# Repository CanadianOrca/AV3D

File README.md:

# AV3D
AV3D or Avid as is our nickname, is an acoustophoretic volumetric display. It will be able to display 3D objects using acoustic radiation forces to levitate and rapidly move a small physical particle. We utilize a fast computer and synchronized LEDs to iterate a Persistence of Vision effect, making the fast bead appear 3D.

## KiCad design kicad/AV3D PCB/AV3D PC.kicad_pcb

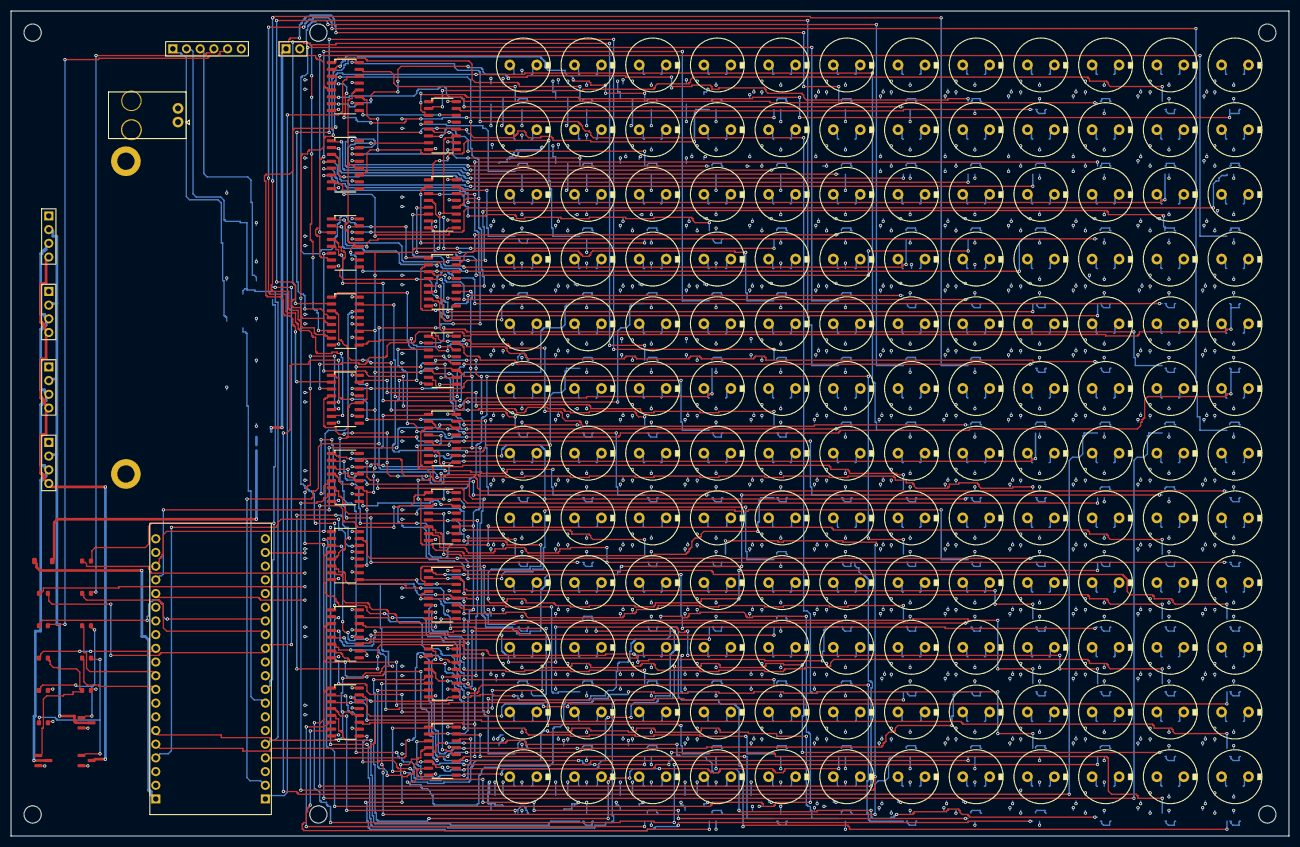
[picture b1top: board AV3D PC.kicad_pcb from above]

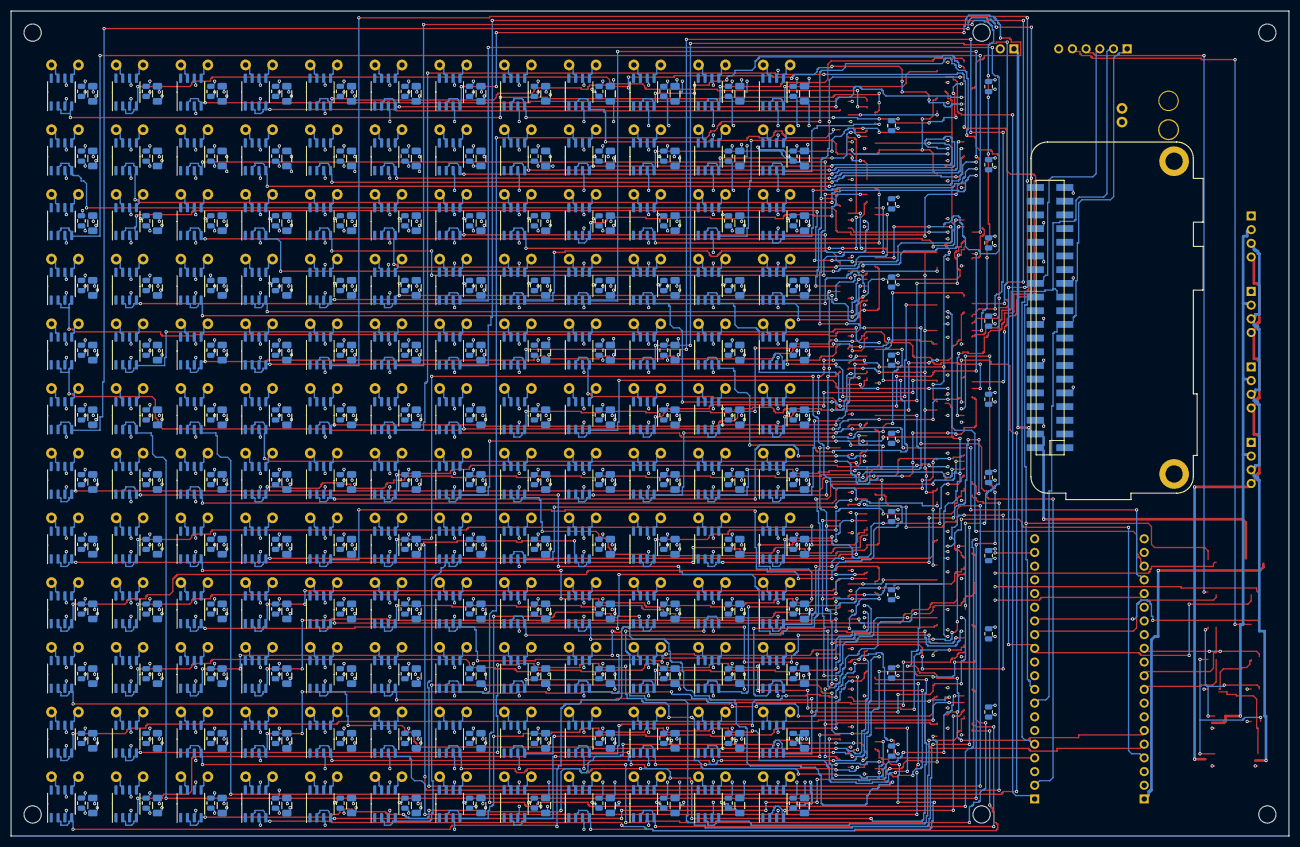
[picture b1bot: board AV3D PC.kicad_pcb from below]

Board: 4 copper layers, 237.0 x 153.0 mm, 641 parts (451 on the bottom side), 474 nets.

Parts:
A1: Raspberry_Pi_2_3; Raspberry_Pi_Zero_Socketed_THT_MountingHoles_SMT
A2: Tang Nano 20K; TangNano20K_2x20
C1, C2, C3, C4, C5, C6, C7, C8, C9, C10, C11, C12, C13, C14, C15, C16, C17, C18, C19, C20, C21, C22, C23, C24, C25, C26, C27, C28, C29, C30, C31, C32, C33, C34, C35, C36, C37, C38, C39, C40, C41, C42, C43, C44, C45, C46, C47, C48, C49, C50, C51, C52, C53, C54, C55, C56, C57, C58, C59, C60, C61, C62, C63, C64, C65, C66, C67, C68, C69, C70, C71, C72, C73, C74, C75, C76, C77, C78, C79, C80, C81, C82, C83, C84, C85, C86, C87, C88, C89, C90, C91, C92, C93, C94, C95, C96, C97, C98, C99, C100, C101, C102, C103, C104, C105, C106, C107, C108, C109, C110, C111, C112, C113, C114, C115, C116, C117, C118, C119, C120, C121, C122, C123, C124, C125, C126, C127, C128, C129, C130, C131, C132, C133, C134, C135, C136, C137, C138, C139, C140, C141, C142, C143, C144: 4.7uF, 35V; C_1206_3216Metric
C145, C146, C147, C148, C149, C150, C151, C152, C153, C154, C155, C156, C157, C158, C159, C160, C161, C162, C163, C164, C165, C166, C167, C168, C169, C170, C171, C172, C173, C174, C175, C176, C177, C178, C179, C180, C181, C182, C183, C184, C185, C186, C187, C188, C189, C190, C191, C192, C193, C194, C195, C196, C197, C198, C199, C200, C201, C202, C203, C204, C205, C206, C207, C208, C209, C210, C211, C212, C213, C214, C215, C216, C217, C218, C219, C220, C221, C222, C223, C224, C225, C226, C227, C228, C229, C230, C231, C232, C233, C234, C235, C236, C237, C238, C239, C240, C241, C242, C243, C244, C245, C246, C247, C248, C249, C250, C251, C252, C253, C254, C255, C256, C257, C258, C259, C260, C261, C262, C263, C264, C265, C266, C267, C268, C269, C270, C271, C272, C273, C274, C275, C276, C277, C278, C279, C280, C281, C282, C283, C284, C285, C286, C287, C288, C289, C290, C291, C292, C293, C294, C295, C296, C297, C298, C299, C300, C301, C302, C303, C304, C305, C306: 0.1uF, 35V; C_0805_2012Metric
D1: 1N5819WS; D_SOD-123
H1, H2, H3, H4, H5, H6: MountingHole; MountingHole_3.2mm_M3
J1: Power; Molex_70555_RA_1x02_P2.54
J2: LED 1 (12V common anode); PinHeader_1x04_P2.54mm_Vertical
J3: LED 2 (12V common anode); PinHeader_1x04_P2.54mm_Vertical
J4: LED 3 (12V common anode); PinHeader_1x04_P2.54mm_Vertical
J5: LED 4 (12V common anode); PinHeader_1x04_P2.54mm_Vertical
J6: BOARD LINK; PinHeader_1x06_P2.54mm_Vertical
J7: 5V IN; PinHeader_1x02_P2.54mm_Vertical
LS1, LS2, LS3, LS4, LS5, LS6, LS7, LS8, LS9, LS10, LS11, LS12, LS13, LS14, LS15, LS16, LS17, LS18, LS19, LS20, LS21, LS22, LS23, LS24, LS25, LS26, LS27, LS28, LS29, LS30, LS31, LS32, LS33, LS34, LS35, LS36, LS37, LS38, LS39, LS40, LS41, LS42, LS43, LS44, LS45, LS46, LS47, LS48, LS49, LS50, LS51, LS52, LS53, LS54, LS55, LS56, LS57, LS58, LS59, LS60, LS61, LS62, LS63, LS64, LS65, LS66, LS67, LS68, LS69, LS70, LS71, LS72, LS73, LS74, LS75, LS76, LS77, LS78, LS79, LS80, LS81, LS82, LS83, LS84, LS85, LS86, LS87, LS88, LS89, LS90, LS91, LS92, LS93, LS94, LS95, LS96, LS97, LS98, LS99, LS100, LS101, LS102, LS103, LS104, LS105, LS106, LS107, LS108, LS109, LS110, LS111, LS112, LS113, LS114, LS115, LS116, LS117, LS118, LS119, LS120, LS121, LS122, LS123, LS124, LS125, LS126, LS127, LS128, LS129, LS130, LS131, LS132, LS133, LS134, LS135, LS136, LS137, LS138, LS139, LS140, LS141, LS142, LS143, LS144: Speaker_Ultrasound; MSO-P1040H07T
Q1, Q2, Q3: AO3400A; SOT-23
R1, R2: 10k; R_0603_1608Metric
R3, R4, R5, R6, R7: 100; R_0603_1608Metric
R8, R9, R10: 100k; R_0603_1608Metric
U1, U2, U3, U4, U5, U6, U7, U8, U9, U10, U11, U12, U13, U14, U15, U16, U17, U18, U19, U20, U21, U22, U23, U24, U25, U26, U27, U28, U29, U30, U31, U32, U33, U34, U35, U36, U37, U38, U39, U40, U41, U42, U43, U44, U45, U46, U47, U48, U49, U50, U51, U52, U53, U54, U55, U56, U57, U58, U59, U60, U61, U62, U63, U64, U65, U66, U67, U68, U69, U70, U71, U72, U73, U74, U75, U76, U77, U78, U79, U80, U81, U82, U83, U84, U85, U86, U87, U88, U89, U90, U91, U92, U93, U94, U95, U96, U97, U98, U99, U100, U101, U102, U103, U104, U105, U106, U107, U108, U109, U110, U111, U112, U113, U114, U115, U116, U117, U118, U119, U120, U121, U122, U123, U124, U125, U126, U127, U128, U129, U130, U131, U132, U133, U134, U135, U136, U137, U138, U139, U140, U141, U142, U143, U144: TC4428A; SO-8_3.9x4.9mm_P1.27mm
U145, U146, U147, U148, U149, U150, U151, U152, U153, U154, U155, U156, U157, U158, U159, U160, U161, U162: 74AHC595; SOIC-16_3.9x9.9mm_P1.27mm

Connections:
+3V3: A2.16, A2.39, C289.1, C290.1, C291.1, C292.1, C293.1, C294.1, C295.1, C296.1, C297.1, C298.1, C299.1, C300.1, C301.1, C302.1, C303.1, C304.1, C305.1, C306.1, R1.1, R2.1, U145.10, U145.16, U146.10, U146.16, U147.10, U147.16, U148.10, U148.16, U149.10, U149.16, U150.10, U150.16, U151.10, U151.16, U152.10, U152.16, U153.10, U153.16, U154.10, U154.16, U155.10, U155.16, U156.10, U156.16, U157.10, U157.16, U158.10, U158.16, U159.10, U159.16, U160.10, U160.16, U161.10, U161.16, U162.10, U162.16
+5V: A1.2, A1.4, D1.2, J7.1
+5V_TANG: A2.1, D1.1
+12V: C1.1, C2.1, C3.1, C4.1, C5.1, C6.1, C7.1, C8.1, C9.1, C10.1, C11.1, C12.1, C13.1, C14.1, C15.1, C16.1, C17.1, C18.1, C19.1, C20.1, C21.1, C22.1, C23.1, C24.1, C25.1, C26.1, C27.1, C28.1, C29.1, C30.1, C31.1, C32.1, C33.1, C34.1, C35.1, C36.1, C37.1, C38.1, C39.1, C40.1, C41.1, C42.1, C43.1, C44.1, C45.1, C46.1, C47.1, C48.1, C49.1, C50.1, C51.1, C52.1, C53.1, C54.1, C55.1, C56.1, C57.1, C58.1, C59.1, C60.1, C61.1, C62.1, C63.1, C64.1, C65.1, C66.1, C67.1, C68.1, C69.1, C70.1, C71.1, C72.1, C73.1, C74.1, C75.1, C76.1, C77.1, C78.1, C79.1, C80.1, C81.1, C82.1, C83.1, C84.1, C85.1, C86.1, C87.1, C88.1, C89.1, C90.1, C91.1, C92.1, C93.1, C94.1, C95.1, C96.1, C97.1, C98.1, C99.1, C100.1, C101.1, C102.1, C103.1, C104.1, C105.1, C106.1, C107.1, C108.1, C109.1, C110.1, C111.1, C112.1, C113.1, C114.1, C115.1, C116.1, C117.1, C118.1, C119.1, C120.1, C121.1, C122.1, C123.1, C124.1, C125.1, C126.1, C127.1, C128.1, C129.1, C130.1, C131.1, C132.1, C133.1, C134.1, C135.1, C136.1, C137.1, C138.1, C139.1, C140.1, C141.1, C142.1, C143.1, C144.1, C145.1, C146.1, C147.1, C148.1, C149.1, C150.1, C151.1, C152.1, C153.1, C154.1, C155.1, C156.1, C157.1, C158.1, C159.1, C160.1, C161.1, C162.1, C163.1, C164.1, C165.1, C166.1, C167.1, C168.1, C169.1, C170.1, C171.1, C172.1, C173.1, C174.1, C175.1, C176.1, C177.1, C178.1, C179.1, C180.1, C181.1, C182.1, C183.1, C184.1, C185.1, C186.1, C187.1, C188.1, C189.1, C190.1, C191.1, C192.1, C193.1, C194.1, C195.1, C196.1, C197.1, C198.1, C199.1, C200.1, C201.1, C202.1, C203.1, C204.1, C205.1, C206.1, C207.1, C208.1, C209.1, C210.1, C211.1, C212.1, C213.1, C214.1, C215.1, C216.1, C217.1, C218.1, C219.1, C220.1, C221.1, C222.1, C223.1, C224.1, C225.1, C226.1, C227.1, C228.1, C229.1, C230.1, C231.1, C232.1, C233.1, C234.1, C235.1, C236.1, C237.1, C238.1, C239.1, C240.1, C241.1, C242.1, C243.1, C244.1, C245.1, C246.1, C247.1, C248.1, C249.1, C250.1, C251.1, C252.1, C253.1, C254.1, C255.1, C256.1, C257.1, C258.1, C259.1, C260.1, C261.1, C262.1, C263.1, C264.1, C265.1, C266.1, C267.1, C268.1, C269.1, C270.1, C271.1, C272.1, C273.1, C274.1, C275.1, C276.1, C277.1, C278.1, C279.1, C280.1, C281.1, C282.1, C283.1, C284.1, C285.1, C286.1, C287.1, C288.1, J1.1, J2.1, J3.1, J4.1, J5.1, U1.6, U2.6, U3.6, U4.6, U5.6, U6.6, U7.6, U8.6, U9.6, U10.6, U11.6, U12.6, U13.6, U14.6, U15.6, U16.6, U17.6, U18.6, U19.6, U20.6, U21.6, U22.6, U23.6, U24.6, U25.6, U26.6, U27.6, U28.6, U29.6, U30.6, U31.6, U32.6, U33.6, U34.6, U35.6, U36.6, U37.6, U38.6, U39.6, U40.6, U41.6, U42.6, U43.6, U44.6, U45.6, U46.6, U47.6, U48.6, U49.6, U50.6, U51.6, U52.6, U53.6, U54.6, U55.6, U56.6, U57.6, U58.6, U59.6, U60.6, U61.6, U62.6, U63.6, U64.6, U65.6, U66.6, U67.6, U68.6, U69.6, U70.6, U71.6, U72.6, U73.6, U74.6, U75.6, U76.6, U77.6, U78.6, U79.6, U80.6, U81.6, U82.6, U83.6, U84.6, U85.6, U86.6, U87.6, U88.6, U89.6, U90.6, U91.6, U92.6, U93.6, U94.6, U95.6, U96.6, U97.6, U98.6, U99.6, U100.6, U101.6, U102.6, U103.6, U104.6, U105.6, U106.6, U107.6, U108.6, U109.6, U110.6, U111.6, U112.6, U113.6, U114.6, U115.6, U116.6, U117.6, U118.6, U119.6, U120.6, U121.6, U122.6, U123.6, U124.6, U125.6, U126.6, U127.6, U128.6, U129.6, U130.6, U131.6, U132.6, U133.6, U134.6, U135.6, U136.6, U137.6, U138.6, U139.6, U140.6, U141.6, U142.6, U143.6, U144.6
CH1: U1.2, U1.4, U145.15
CH2: U2.2, U2.4, U145.1
CH3: U3.2, U3.4, U145.2
CH4: U4.2, U4.4, U145.3
CH5: U5.2, U5.4, U145.4
CH6: U6.2, U6.4, U145.5
CH7: U7.2, U7.4, U145.6
CH8: U8.2, U8.4, U145.7
CH9: U9.2, U9.4, U146.15
CH10: U10.2, U10.4, U146.1
CH11: U11.2, U11.4, U146.2
CH12: U12.2, U12.4, U146.3
CH13: U13.2, U13.4, U146.4
CH14: U14.2, U14.4, U146.5
CH15: U15.2, U15.4, U146.6
CH16: U16.2, U16.4, U146.7
CH17: U17.2, U17.4, U147.15
CH18: U18.2, U18.4, U147.1
CH19: U19.2, U19.4, U147.2
CH20: U20.2, U20.4, U147.3
CH21: U21.2, U21.4, U147.4
CH22: U22.2, U22.4, U147.5
CH23: U23.2, U23.4, U147.6
CH24: U24.2, U24.4, U147.7
CH25: U25.2, U25.4, U148.15
CH26: U26.2, U26.4, U148.1
CH27: U27.2, U27.4, U148.2
CH28: U28.2, U28.4, U148.3
CH29: U29.2, U29.4, U148.4
CH30: U30.2, U30.4, U148.5
CH31: U31.2, U31.4, U148.6
CH32: U32.2, U32.4, U148.7
CH33: U33.2, U33.4, U149.15
CH34: U34.2, U34.4, U149.1
CH35: U35.2, U35.4, U149.2
CH36: U36.2, U36.4, U149.3
CH37: U37.2, U37.4, U149.4
CH38: U38.2, U38.4, U149.5
CH39: U39.2, U39.4, U149.6
CH40: U40.2, U40.4, U149.7
CH41: U41.2, U41.4, U150.15
CH42: U42.2, U42.4, U150.1
CH43: U43.2, U43.4, U150.2
CH44: U44.2, U44.4, U150.3
CH45: U45.2, U45.4, U150.4
CH46: U46.2, U46.4, U150.5
CH47: U47.2, U47.4, U150.6
CH48: U48.2, U48.4, U150.7
CH49: U49.2, U49.4, U151.15
CH50: U50.2, U50.4, U151.1
CH51: U51.2, U51.4, U151.2
CH52: U52.2, U52.4, U151.3
CH53: U53.2, U53.4, U151.4
CH54: U54.2, U54.4, U151.5
CH55: U55.2, U55.4, U151.6
CH56: U56.2, U56.4, U151.7
CH57: U57.2, U57.4, U152.15
CH58: U58.2, U58.4, U152.1
CH59: U59.2, U59.4, U152.2
CH60: U60.2, U60.4, U152.3
CH61: U61.2, U61.4, U152.4
CH62: U62.2, U62.4, U152.5
CH63: U63.2, U63.4, U152.6
CH64: U64.2, U64.4, U152.7
CH65: U65.2, U65.4, U153.15
CH66: U66.2, U66.4, U153.1
CH67: U67.2, U67.4, U153.2
CH68: U68.2, U68.4, U153.3
CH69: U69.2, U69.4, U153.4
CH70: U70.2, U70.4, U153.5
CH71: U71.2, U71.4, U153.6
CH72: U72.2, U72.4, U153.7
CH73: U73.2, U73.4, U154.15
CH74: U74.2, U74.4, U154.1
CH75: U75.2, U75.4, U154.2
CH76: U76.2, U76.4, U154.3
CH77: U77.2, U77.4, U154.4
CH78: U78.2, U78.4, U154.5
CH79: U79.2, U79.4, U154.6
CH80: U80.2, U80.4, U154.7
CH81: U81.2, U81.4, U155.15
CH82: U82.2, U82.4, U155.1
CH83: U83.2, U83.4, U155.2
CH84: U84.2, U84.4, U155.3
CH85: U85.2, U85.4, U155.4
CH86: U86.2, U86.4, U155.5
CH87: U87.2, U87.4, U155.6
CH88: U88.2, U88.4, U155.7
CH89: U89.2, U89.4, U156.15
CH90: U90.2, U90.4, U156.1
CH91: U91.2, U91.4, U156.2
CH92: U92.2, U92.4, U156.3
CH93: U93.2, U93.4, U156.4
CH94: U94.2, U94.4, U156.5
CH95: U95.2, U95.4, U156.6
CH96: U96.2, U96.4, U156.7
CH97: U97.2, U97.4, U157.15
CH98: U98.2, U98.4, U157.1
CH99: U99.2, U99.4, U157.2
CH100: U100.2, U100.4, U157.3
CH101: U101.2, U101.4, U157.4
CH102: U102.2, U102.4, U157.5
CH103: U103.2, U103.4, U157.6
CH104: U104.2, U104.4, U157.7
CH105: U105.2, U105.4, U158.15
CH106: U106.2, U106.4, U158.1
CH107: U107.2, U107.4, U158.2
CH108: U108.2, U108.4, U158.3
CH109: U109.2, U109.4, U158.4
CH110: U110.2, U110.4, U158.5
CH111: U111.2, U111.4, U158.6
CH112: U112.2, U112.4, U158.7
CH113: U113.2, U113.4, U159.15
CH114: U114.2, U114.4, U159.1
CH115: U115.2, U115.4, U159.2
CH116: U116.2, U116.4, U159.3
CH117: U117.2, U117.4, U159.4
CH118: U118.2, U118.4, U159.5
CH119: U119.2, U119.4, U159.6
CH120: U120.2, U120.4, U159.7
CH121: U121.2, U121.4, U160.15
CH122: U122.2, U122.4, U160.1
CH123: U123.2, U123.4, U160.2
CH124: U124.2, U124.4, U160.3
CH125: U125.2, U125.4, U160.4
CH126: U126.2, U126.4, U160.5
CH127: U127.2, U127.4, U160.6
CH128: U128.2, U128.4, U160.7
CH129: U129.2, U129.4, U161.15
CH130: U130.2, U130.4, U161.1
CH131: U131.2, U131.4, U161.2
CH132: U132.2, U132.4, U161.3
CH133: U133.2, U133.4, U161.4
CH134: U134.2, U134.4, U161.5
CH135: U135.2, U135.4, U161.6
CH136: U136.2, U136.4, U161.7
CH137: U137.2, U137.4, U162.15
CH138: U138.2, U138.4, U162.1
CH139: U139.2, U139.4, U162.2
CH140: U140.2, U140.4, U162.3
CH141: U141.2, U141.4, U162.4
CH142: U142.2, U142.4, U162.5
CH143: U143.2, U143.4, U162.6
CH144: U144.2, U144.4, U162.7
GATE_B: Q3.1, R7.2, R10.1
GATE_G: Q2.1, R6.2, R9.1
GATE_R: Q1.1, R5.2, R8.1
GND: A1.6, A1.9, A1.14, A1.20, A1.25, A1.30, A1.34, A1.39, A2.2, A2.15, A2.40, C1.2, C2.2, C3.2, C4.2, C5.2, C6.2, C7.2, C8.2, C9.2, C10.2, C11.2, C12.2, C13.2, C14.2, C15.2, C16.2, C17.2, C18.2, C19.2, C20.2, C21.2, C22.2, C23.2, C24.2, C25.2, C26.2, C27.2, C28.2, C29.2, C30.2, C31.2, C32.2, C33.2, C34.2, C35.2, C36.2, C37.2, C38.2, C39.2, C40.2, C41.2, C42.2, C43.2, C44.2, C45.2, C46.2, C47.2, C48.2, C49.2, C50.2, C51.2, C52.2, C53.2, C54.2, C55.2, C56.2, C57.2, C58.2, C59.2, C60.2, C61.2, C62.2, C63.2, C64.2, C65.2, C66.2, C67.2, C68.2, C69.2, C70.2, C71.2, C72.2, C73.2, C74.2, C75.2, C76.2, C77.2, C78.2, C79.2, C80.2, C81.2, C82.2, C83.2, C84.2, C85.2, C86.2, C87.2, C88.2, C89.2, C90.2, C91.2, C92.2, C93.2, C94.2, C95.2, C96.2, C97.2, C98.2, C99.2, C100.2, C101.2, C102.2, C103.2, C104.2, C105.2, C106.2, C107.2, C108.2, C109.2, C110.2, C111.2, C112.2, C113.2, C114.2, C115.2, C116.2, C117.2, C118.2, C119.2, C120.2, C121.2, C122.2, C123.2, C124.2, C125.2, C126.2, C127.2, C128.2, C129.2, C130.2, C131.2, C132.2, C133.2, C134.2, C135.2, C136.2, C137.2, C138.2, C139.2, C140.2, C141.2, C142.2, C143.2, C144.2, C145.2, C146.2, C147.2, C148.2, C149.2, C150.2, C151.2, C152.2, C153.2, C154.2, C155.2, C156.2, C157.2, C158.2, C159.2, C160.2, C161.2, C162.2, C163.2, C164.2, C165.2, C166.2, C167.2, C168.2, C169.2, C170.2, C171.2, C172.2, C173.2, C174.2, C175.2, C176.2, C177.2, C178.2, C179.2, C180.2, C181.2, C182.2, C183.2, C184.2, C185.2, C186.2, C187.2, C188.2, C189.2, C190.2, C191.2, C192.2, C193.2, C194.2, C195.2, C196.2, C197.2, C198.2, C199.2, C200.2, C201.2, C202.2, C203.2, C204.2, C205.2, C206.2, C207.2, C208.2, C209.2, C210.2, C211.2, C212.2, C213.2, C214.2, C215.2, C216.2, C217.2, C218.2, C219.2, C220.2, C221.2, C222.2, C223.2, C224.2, C225.2, C226.2, C227.2, C228.2, C229.2, C230.2, C231.2, C232.2, C233.2, C234.2, C235.2, C236.2, C237.2, C238.2, C239.2, C240.2, C241.2, C242.2, C243.2, C244.2, C245.2, C246.2, C247.2, C248.2, C249.2, C250.2, C251.2, C252.2, C253.2, C254.2, C255.2, C256.2, C257.2, C258.2, C259.2, C260.2, C261.2, C262.2, C263.2, C264.2, C265.2, C266.2, C267.2, C268.2, C269.2, C270.2, C271.2, C272.2, C273.2, C274.2, C275.2, C276.2, C277.2, C278.2, C279.2, C280.2, C281.2, C282.2, C283.2, C284.2, C285.2, C286.2, C287.2, C288.2, C289.2, C290.2, C291.2, C292.2, C293.2, C294.2, C295.2, C296.2, C297.2, C298.2, C299.2, C300.2, C301.2, C302.2, C303.2, C304.2, C305.2, C306.2, J1.2, J6.6, J7.2, Q1.2, Q2.2, Q3.2, R8.2, R9.2, R10.2, U1.3, U2.3, U3.3, U4.3, U5.3, U6.3, U7.3, U8.3, U9.3, U10.3, U11.3, U12.3, U13.3, U14.3, U15.3, U16.3, U17.3, U18.3, U19.3, U20.3, U21.3, U22.3, U23.3, U24.3, U25.3, U26.3, U27.3, U28.3, U29.3, U30.3, U31.3, U32.3, U33.3, U34.3, U35.3, U36.3, U37.3, U38.3, U39.3, U40.3, U41.3, U42.3, U43.3, U44.3, U45.3, U46.3, U47.3, U48.3, U49.3, U50.3, U51.3, U52.3, U53.3, U54.3, U55.3, U56.3, U57.3, U58.3, U59.3, U60.3, U61.3, U62.3, U63.3, U64.3, U65.3, U66.3, U67.3, U68.3, U69.3, U70.3, U71.3, U72.3, U73.3, U74.3, U75.3, U76.3, U77.3, U78.3, U79.3, U80.3, U81.3, U82.3, U83.3, U84.3, U85.3, U86.3, U87.3, U88.3, U89.3, U90.3, U91.3, U92.3, U93.3, U94.3, U95.3, U96.3, U97.3, U98.3, U99.3, U100.3, U101.3, U102.3, U103.3, U104.3, U105.3, U106.3, U107.3, U108.3, U109.3, U110.3, U111.3, U112.3, U113.3, U114.3, U115.3, U116.3, U117.3, U118.3, U119.3, U120.3, U121.3, U122.3, U123.3, U124.3, U125.3, U126.3, U127.3, U128.3, U129.3, U130.3, U131.3, U132.3, U133.3, U134.3, U135.3, U136.3, U137.3, U138.3, U139.3, U140.3, U141.3, U142.3, U143.3, U144.3, U145.8, U145.13, U146.8, U146.13, U147.8, U147.13, U148.8, U148.13, U149.8, U149.13, U150.8, U150.13, U151.8, U151.13, U152.8, U152.13, U153.8, U153.13, U154.8, U154.13, U155.8, U155.13, U156.8, U156.13, U157.8, U157.13, U158.8, U158.13, U159.8, U159.13, U160.8, U160.13, U161.8, U161.13, U162.8, U162.13
LEDK_B: J2.4, J3.4, J4.4, J5.4, Q3.3
LEDK_G: J2.3, J3.3, J4.3, J5.3, Q2.3
LEDK_R: J2.2, J3.2, J4.2, J5.2, Q1.3
LED_B: A2.9, R7.1
LED_G: A2.12, R6.1
LED_R: A2.10, R5.1
NEXT: A2.34, R4.1
NEXT_LINK: J6.5, R4.2
OUT1_1: LS1.1, U1.7
OUT1_2: LS1.2, U1.5
OUT2_1: LS2.1, U2.7
OUT2_2: LS2.2, U2.5
OUT3_1: LS3.1, U3.7
OUT3_2: LS3.2, U3.5
OUT4_1: LS4.1, U4.7
OUT4_2: LS4.2, U4.5
OUT5_1: LS5.1, U5.7
OUT5_2: LS5.2, U5.5
OUT6_1: LS6.1, U6.7
OUT6_2: LS6.2, U6.5
OUT7_1: LS7.1, U7.7
OUT7_2: LS7.2, U7.5
OUT8_1: LS8.1, U8.7
OUT8_2: LS8.2, U8.5
OUT9_1: LS9.1, U9.7
OUT9_2: LS9.2, U9.5
OUT10_1: LS10.1, U10.7
OUT10_2: LS10.2, U10.5
OUT11_1: LS11.1, U11.7
OUT11_2: LS11.2, U11.5
OUT12_1: LS12.1, U12.7
OUT12_2: LS12.2, U12.5
OUT13_1: LS13.1, U13.7
OUT13_2: LS13.2, U13.5
OUT14_1: LS14.1, U14.7
OUT14_2: LS14.2, U14.5
OUT15_1: LS15.1, U15.7
OUT15_2: LS15.2, U15.5
OUT16_1: LS16.1, U16.7
OUT16_2: LS16.2, U16.5
OUT17_1: LS17.1, U17.7
OUT17_2: LS17.2, U17.5
OUT18_1: LS18.1, U18.7
OUT18_2: LS18.2, U18.5
OUT19_1: LS19.1, U19.7
OUT19_2: LS19.2, U19.5
OUT20_1: LS20.1, U20.7
OUT20_2: LS20.2, U20.5
OUT21_1: LS21.1, U21.7
OUT21_2: LS21.2, U21.5
OUT22_1: LS22.1, U22.7
OUT22_2: LS22.2, U22.5
OUT23_1: LS23.1, U23.7
OUT23_2: LS23.2, U23.5
OUT24_1: LS24.1, U24.7
OUT24_2: LS24.2, U24.5
OUT25_1: LS25.1, U25.7
OUT25_2: LS25.2, U25.5
OUT26_1: LS26.1, U26.7
OUT26_2: LS26.2, U26.5
OUT27_1: LS27.1, U27.7
OUT27_2: LS27.2, U27.5
OUT28_1: LS28.1, U28.7
OUT28_2: LS28.2, U28.5
OUT29_1: LS29.1, U29.7
OUT29_2: LS29.2, U29.5
OUT30_1: LS30.1, U30.7
OUT30_2: LS30.2, U30.5
OUT31_1: LS31.1, U31.7
OUT31_2: LS31.2, U31.5
OUT32_1: LS32.1, U32.7
OUT32_2: LS32.2, U32.5
OUT33_1: LS33.1, U33.7
OUT33_2: LS33.2, U33.5
OUT34_1: LS34.1, U34.7
OUT34_2: LS34.2, U34.5
OUT35_1: LS35.1, U35.7
OUT35_2: LS35.2, U35.5
OUT36_1: LS36.1, U36.7
OUT36_2: LS36.2, U36.5
OUT37_1: LS37.1, U37.7
OUT37_2: LS37.2, U37.5
OUT38_1: LS38.1, U38.7
OUT38_2: LS38.2, U38.5
OUT39_1: LS39.1, U39.7
OUT39_2: LS39.2, U39.5
OUT40_1: LS40.1, U40.7
OUT40_2: LS40.2, U40.5
OUT41_1: LS41.1, U41.7
OUT41_2: LS41.2, U41.5
OUT42_1: LS42.1, U42.7
OUT42_2: LS42.2, U42.5
OUT43_1: LS43.1, U43.7
OUT43_2: LS43.2, U43.5
OUT44_1: LS44.1, U44.7
OUT44_2: LS44.2, U44.5
OUT45_1: LS45.1, U45.7
OUT45_2: LS45.2, U45.5
OUT46_1: LS46.1, U46.7
OUT46_2: LS46.2, U46.5
OUT47_1: LS47.1, U47.7
OUT47_2: LS47.2, U47.5
OUT48_1: LS48.1, U48.7
OUT48_2: LS48.2, U48.5
OUT49_1: LS49.1, U49.7
OUT49_2: LS49.2, U49.5
OUT50_1: LS50.1, U50.7
OUT50_2: LS50.2, U50.5
OUT51_1: LS51.1, U51.7
OUT51_2: LS51.2, U51.5
OUT52_1: LS52.1, U52.7
OUT52_2: LS52.2, U52.5
OUT53_1: LS53.1, U53.7
OUT53_2: LS53.2, U53.5
OUT54_1: LS54.1, U54.7
OUT54_2: LS54.2, U54.5
OUT55_1: LS55.1, U55.7
OUT55_2: LS55.2, U55.5
OUT56_1: LS56.1, U56.7
OUT56_2: LS56.2, U56.5
OUT57_1: LS57.1, U57.7
OUT57_2: LS57.2, U57.5
OUT58_1: LS58.1, U58.7
OUT58_2: LS58.2, U58.5
OUT59_1: LS59.1, U59.7
OUT59_2: LS59.2, U59.5
OUT60_1: LS60.1, U60.7
OUT60_2: LS60.2, U60.5
OUT61_1: LS61.1, U61.7
OUT61_2: LS61.2, U61.5
OUT62_1: LS62.1, U62.7
OUT62_2: LS62.2, U62.5
OUT63_1: LS63.1, U63.7
OUT63_2: LS63.2, U63.5
OUT64_1: LS64.1, U64.7
OUT64_2: LS64.2, U64.5
OUT65_1: LS65.1, U65.7
OUT65_2: LS65.2, U65.5
OUT66_1: LS66.1, U66.7
OUT66_2: LS66.2, U66.5
OUT67_1: LS67.1, U67.7
OUT67_2: LS67.2, U67.5
OUT68_1: LS68.1, U68.7
OUT68_2: LS68.2, U68.5
OUT69_1: LS69.1, U69.7
OUT69_2: LS69.2, U69.5
OUT70_1: LS70.1, U70.7
OUT70_2: LS70.2, U70.5
OUT71_1: LS71.1, U71.7
OUT71_2: LS71.2, U71.5
OUT72_1: LS72.1, U72.7
OUT72_2: LS72.2, U72.5
OUT73_1: LS73.1, U73.7
OUT73_2: LS73.2, U73.5
OUT74_1: LS74.1, U74.7
OUT74_2: LS74.2, U74.5
OUT75_1: LS75.1, U75.7
OUT75_2: LS75.2, U75.5
OUT76_1: LS76.1, U76.7
OUT76_2: LS76.2, U76.5
OUT77_1: LS77.1, U77.7
OUT77_2: LS77.2, U77.5
OUT78_1: LS78.1, U78.7
OUT78_2: LS78.2, U78.5
OUT79_1: LS79.1, U79.7
OUT79_2: LS79.2, U79.5
OUT80_1: LS80.1, U80.7
OUT80_2: LS80.2, U80.5
OUT81_1: LS81.1, U81.7
OUT81_2: LS81.2, U81.5
OUT82_1: LS82.1, U82.7
OUT82_2: LS82.2, U82.5
OUT83_1: LS83.1, U83.7
OUT83_2: LS83.2, U83.5
OUT84_1: LS84.1, U84.7
OUT84_2: LS84.2, U84.5
OUT85_1: LS85.1, U85.7
OUT85_2: LS85.2, U85.5
OUT86_1: LS86.1, U86.7
OUT86_2: LS86.2, U86.5
OUT87_1: LS87.1, U87.7
OUT87_2: LS87.2, U87.5
OUT88_1: LS88.1, U88.7
OUT88_2: LS88.2, U88.5
OUT89_1: LS89.1, U89.7
OUT89_2: LS89.2, U89.5
OUT90_1: LS90.1, U90.7
OUT90_2: LS90.2, U90.5
OUT91_1: LS91.1, U91.7
OUT91_2: LS91.2, U91.5
OUT92_1: LS92.1, U92.7
OUT92_2: LS92.2, U92.5
OUT93_1: LS93.1, U93.7
OUT93_2: LS93.2, U93.5
OUT94_1: LS94.1, U94.7
OUT94_2: LS94.2, U94.5
OUT95_1: LS95.1, U95.7
OUT95_2: LS95.2, U95.5
OUT96_1: LS96.1, U96.7
OUT96_2: LS96.2, U96.5
OUT97_1: LS97.1, U97.7
OUT97_2: LS97.2, U97.5
OUT98_1: LS98.1, U98.7
OUT98_2: LS98.2, U98.5
OUT99_1: LS99.1, U99.7
OUT99_2: LS99.2, U99.5
OUT100_1: LS100.1, U100.7
OUT100_2: LS100.2, U100.5
OUT101_1: LS101.1, U101.7
OUT101_2: LS101.2, U101.5
OUT102_1: LS102.1, U102.7
OUT102_2: LS102.2, U102.5
OUT103_1: LS103.1, U103.7
OUT103_2: LS103.2, U103.5
OUT104_1: LS104.1, U104.7
OUT104_2: LS104.2, U104.5
OUT105_1: LS105.1, U105.7
OUT105_2: LS105.2, U105.5
OUT106_1: LS106.1, U106.7
OUT106_2: LS106.2, U106.5
OUT107_1: LS107.1, U107.7
OUT107_2: LS107.2, U107.5
OUT108_1: LS108.1, U108.7
OUT108_2: LS108.2, U108.5
OUT109_1: LS109.1, U109.7
OUT109_2: LS109.2, U109.5
OUT110_1: LS110.1, U110.7
OUT110_2: LS110.2, U110.5
OUT111_1: LS111.1, U111.7
OUT111_2: LS111.2, U111.5
OUT112_1: LS112.1, U112.7
OUT112_2: LS112.2, U112.5
OUT113_1: LS113.1, U113.7
OUT113_2: LS113.2, U113.5
OUT114_1: LS114.1, U114.7
OUT114_2: LS114.2, U114.5
OUT115_1: LS115.1, U115.7
OUT115_2: LS115.2, U115.5
OUT116_1: LS116.1, U116.7
OUT116_2: LS116.2, U116.5
OUT117_1: LS117.1, U117.7
OUT117_2: LS117.2, U117.5
OUT118_1: LS118.1, U118.7
OUT118_2: LS118.2, U118.5
OUT119_1: LS119.1, U119.7
OUT119_2: LS119.2, U119.5
OUT120_1: LS120.1, U120.7
OUT120_2: LS120.2, U120.5
OUT121_1: LS121.1, U121.7
OUT121_2: LS121.2, U121.5
OUT122_1: LS122.1, U122.7
OUT122_2: LS122.2, U122.5
OUT123_1: LS123.1, U123.7
OUT123_2: LS123.2, U123.5
OUT124_1: LS124.1, U124.7
OUT124_2: LS124.2, U124.5
OUT125_1: LS125.1, U125.7
OUT125_2: LS125.2, U125.5
OUT126_1: LS126.1, U126.7
OUT126_2: LS126.2, U126.5
OUT127_1: LS127.1, U127.7
OUT127_2: LS127.2, U127.5
OUT128_1: LS128.1, U128.7
OUT128_2: LS128.2, U128.5
OUT129_1: LS129.1, U129.7
OUT129_2: LS129.2, U129.5
OUT130_1: LS130.1, U130.7
OUT130_2: LS130.2, U130.5
OUT131_1: LS131.1, U131.7
OUT131_2: LS131.2, U131.5
OUT132_1: LS132.1, U132.7
OUT132_2: LS132.2, U132.5
OUT133_1: LS133.1, U133.7
OUT133_2: LS133.2, U133.5
OUT134_1: LS134.1, U134.7
OUT134_2: LS134.2, U134.5
OUT135_1: LS135.1, U135.7
OUT135_2: LS135.2, U135.5
OUT136_1: LS136.1, U136.7
OUT136_2: LS136.2, U136.5
OUT137_1: LS137.1, U137.7
OUT137_2: LS137.2, U137.5
OUT138_1: LS138.1, U138.7
OUT138_2: LS138.2, U138.5
OUT139_1: LS139.1, U139.7
OUT139_2: LS139.2, U139.5
OUT140_1: LS140.1, U140.7
OUT140_2: LS140.2, U140.5
OUT141_1: LS141.1, U141.7
OUT141_2: LS141.2, U141.5
OUT142_1: LS142.1, U142.7
OUT142_2: LS142.2, U142.5
OUT143_1: LS143.1, U143.7
OUT143_2: LS143.2, U143.5
OUT144_1: LS144.1, U144.7
OUT144_2: LS144.2, U144.5
RCLK: A2.6, U145.12, U146.12, U147.12, U148.12, U149.12, U150.12, U151.12, U152.12, U153.12, U154.12, U155.12, U156.12, U157.12, U158.12, U159.12, U160.12, U161.12, U162.12
SER1: A2.21, U145.14
SER2: A2.22, U148.14
SER3: A2.18, U151.14
SER4: A2.17, U154.14
SER5: A2.4, U157.14
SER6: A2.24, U160.14
SPI_CE0: A1.24, A2.29, R1.2
SPI_CE1: A1.26, A2.32, J6.3, R2.2
SPI_MOSI: A1.19, A2.28, J6.1
SPI_SCLK: A1.23, A2.25, J6.2
SRCLK: A2.5, U145.11, U146.11, U147.11, U148.11, U149.11, U150.11, U151.11, U152.11, U153.11, U154.11, U155.11, U156.11, U157.11, U158.11, U159.11, U160.11, U161.11, U162.11
SRQ0: U145.9, U146.14
SRQ1: U146.9, U147.14
SRQ3: U148.9, U149.14
SRQ4: U149.9, U150.14
SRQ6: U151.9, U152.14
SRQ7: U152.9, U153.14
SRQ9: U154.9, U155.14
SRQ10: U155.9, U156.14
SRQ12: U157.9, U158.14
SRQ13: U158.9, U159.14
SRQ15: U160.9, U161.14
SRQ16: U161.9, U162.14
SYNC: A2.33, R3.1
SYNC_LINK: J6.4, R3.2

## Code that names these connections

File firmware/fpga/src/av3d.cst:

/* Gowin pin constraints, Sipeed Tang Nano 20k (GW2AR-LV18QN88C8/I7)

the header pins are 15-20, 25-31, 41, 42, 48, 49, 51-56, 71-77, 79, 80, 85, 86.

Nine are wired to pins on the module, so we cannot avoid them. They are used where the extra load will cause no harm.

15-20 onboard LEDs > DATA lines (LEDs flicker)
16 onboard LED1 > /OE (led1 on = drivers on)
79 WS2812 data in > ID (static, so rgb led stays dark)
80, 85 SD CARD d2/d1 (pull up) > DATA lines
25 and 26 (HDMI CEC/HPD) are the 2 spares.
*/

// on the module
IO_LOC  "clk27" 4;
IO_PORT "clk27" IO_TYPE=LVCMOS33 PULL_MODE=UP;
IO_LOC  "btn_s1" 88;
IO_PORT "btn_s1" IO_TYPE=LVCMOS33 PULL_MODE=NONE;

// shift register clocks (clean)
IO_LOC  "sr_clk_a" 27;
IO_PORT "sr_clk_a" IO_TYPE=LVCMOS33 PULL_MODE=NONE DRIVE=8;
IO_LOC  "sr_clk_b" 28;
IO_PORT "sr_clk_b" IO_TYPE=LVCMOS33 PULL_MODE=NONE DRIVE=8;
IO_LOC  "sr_latch" 29;
IO_PORT "sr_latch" IO_TYPE=LVCMOS33 PULL_MODE=NONE DRIVE=8;
IO_LOC  "sr_oe_n" 16;
IO_PORT "sr_oe_n" IO_TYPE=LVCMOS33 PULL_MODE=UP DRIVE=8;

// DATA1..DATA18 > SER of U10..U27
IO_LOC  "sr_data[0]" 75;
IO_PORT "sr_data[0]" IO_TYPE=LVCMOS33 PULL_MODE=NONE DRIVE=8;
IO_LOC  "sr_data[1]" 80;
IO_PORT "sr_data[1]" IO_TYPE=LVCMOS33 PULL_MODE=NONE DRIVE=8;
IO_LOC  "sr_data[2]" 51;
IO_PORT "sr_data[2]" IO_TYPE=LVCMOS33 PULL_MODE=NONE DRIVE=8;
IO_LOC  "sr_data[3]" 49;
IO_PORT "sr_data[3]" IO_TYPE=LVCMOS33 PULL_MODE=NONE DRIVE=8;
IO_LOC  "sr_data[4]" 86;
IO_PORT "sr_data[4]" IO_TYPE=LVCMOS33 PULL_MODE=NONE DRIVE=8;
IO_LOC  "sr_data[5]" 72;
IO_PORT "sr_data[5]" IO_TYPE=LVCMOS33 PULL_MODE=NONE DRIVE=8;
IO_LOC  "sr_data[6]" 71;
IO_PORT "sr_data[6]" IO_TYPE=LVCMOS33 PULL_MODE=NONE DRIVE=8;
IO_LOC  "sr_data[7]" 53;
IO_PORT "sr_data[7]" IO_TYPE=LVCMOS33 PULL_MODE=NONE DRIVE=8;
IO_LOC  "sr_data[8]" 52;
IO_PORT "sr_data[8]" IO_TYPE=LVCMOS33 PULL_MODE=NONE DRIVE=8;
IO_LOC  "sr_data[9]" 73;
IO_PORT "sr_data[9]" IO_TYPE=LVCMOS33 PULL_MODE=NONE DRIVE=8;
IO_LOC  "sr_data[10]" 74;
IO_PORT "sr_data[10]" IO_TYPE=LVCMOS33 PULL_MODE=NONE DRIVE=8;
IO_LOC  "sr_data[11]" 76;
IO_PORT "sr_data[11]" IO_TYPE=LVCMOS33 PULL_MODE=NONE DRIVE=8;
IO_LOC  "sr_data[12]" 85;
IO_PORT "sr_data[12]" IO_TYPE=LVCMOS33 PULL_MODE=NONE DRIVE=8;
IO_LOC  "sr_data[13]" 15;
IO_PORT "sr_data[13]" IO_TYPE=LVCMOS33 PULL_MODE=NONE DRIVE=8;
IO_LOC  "sr_data[14]" 17;
IO_PORT "sr_data[14]" IO_TYPE=LVCMOS33 PULL_MODE=NONE DRIVE=8;
IO_LOC  "sr_data[15]" 20;
IO_PORT "sr_data[15]" IO_TYPE=LVCMOS33 PULL_MODE=NONE DRIVE=8;
IO_LOC  "sr_data[16]" 19;
IO_PORT "sr_data[16]" IO_TYPE=LVCMOS33 PULL_MODE=NONE DRIVE=8;
IO_LOC  "sr_data[17]" 18;
IO_PORT "sr_data[17]" IO_TYPE=LVCMOS33 PULL_MODE=NONE DRIVE=8;

//SPI from the pin
IO_LOC  "spi_sck" 77;
IO_PORT "spi_sck" IO_TYPE=LVCMOS33 PULL_MODE=DOWN;
IO_LOC  "spi_mosi" 30;
IO_PORT "spi_mosi" IO_TYPE=LVCMOS33 PULL_MODE=DOWN;
IO_LOC  "spi_cs_n" 31;
IO_PORT "spi_cs_n" IO_TYPE=LVCMOS33 PULL_MODE=UP;
IO_LOC  "spi_miso" 41;
IO_PORT "spi_miso" IO_TYPE=LVCMOS33 PULL_MODE=NONE DRIVE=8;

// board to board
IO_LOC  "sync_io" 42;
IO_PORT "sync_io" IO_TYPE=LVCMOS33 PULL_MODE=DOWN DRIVE=8;
IO_LOC  "step_io" 48;
IO_PORT "step_io" IO_TYPE=LVCMOS33 PULL_MODE=DOWN DRIVE=8;

// LED mosfet
IO_LOC  "led_r" 54;
IO_PORT "led_r" IO_TYPE=LVCMOS33 PULL_MODE=NONE DRIVE=8;
IO_LOC  "led_g" 55;
IO_PORT "led_g" IO_TYPE=LVCMOS33 PULL_MODE=NONE DRIVE=8;
IO_LOC  "led_b" 56;
IO_PORT "led_b" IO_TYPE=LVCMOS33 PULL_MODE=NONE DRIVE=8;

// board id
IO_LOC  "id_n" 79;
IO_PORT "id_n" IO_TYPE=LVCMOS33 PULL_MODE=UP;
